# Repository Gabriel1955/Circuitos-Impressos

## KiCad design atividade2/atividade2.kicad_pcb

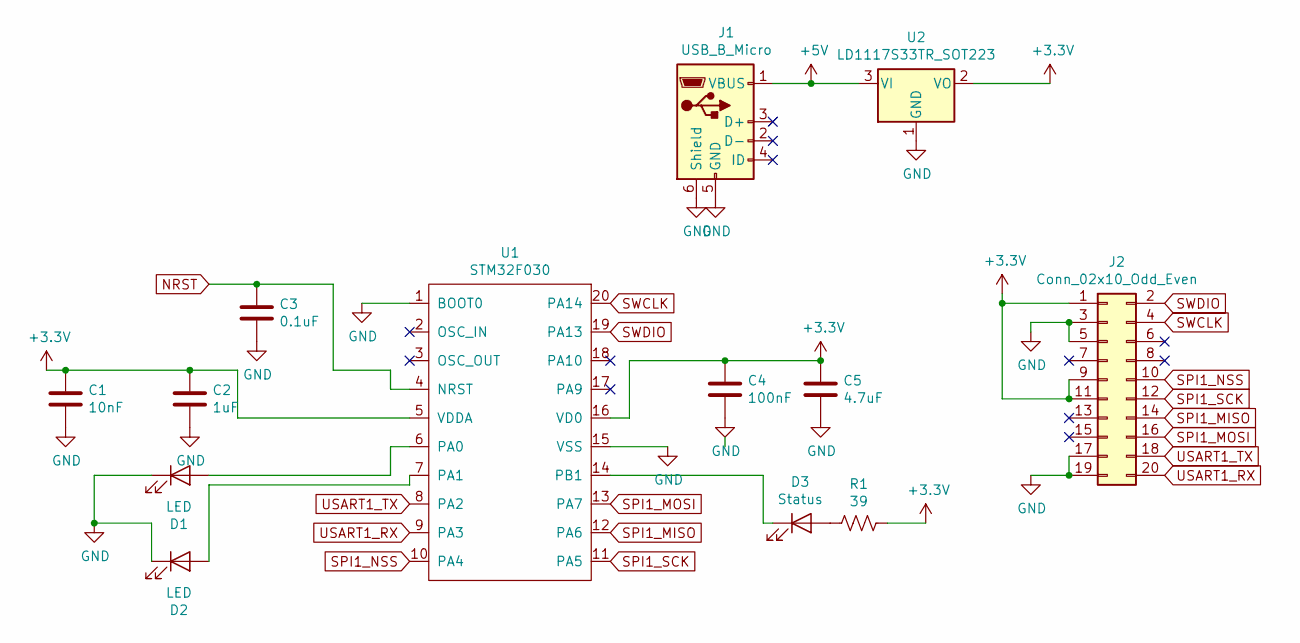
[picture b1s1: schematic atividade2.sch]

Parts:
C1: 10nF; C_0805_2012Metric_Pad1.15x1.40mm_HandSolder
C2: 1uF; C_0805_2012Metric_Pad1.15x1.40mm_HandSolder
C3: 0.1uF; C_0805_2012Metric_Pad1.15x1.40mm_HandSolder
C4: 100nF; C_0805_2012Metric_Pad1.15x1.40mm_HandSolder
C5: 4.7uF; C_0805_2012Metric_Pad1.15x1.40mm_HandSolder
D1, D2: LED; LED_0805_2012Metric_Pad1.15x1.40mm_HandSolder
D3: Status; LED_0805_2012Metric_Pad1.15x1.40mm_HandSolder
J1: USB_B_Micro; USB_Micro-B_Molex-105017-0001
J2: Conn_02x10_Odd_Even; PinHeader_2x10_P2.00mm_Vertical
R1: 39; R_0805_2012Metric_Pad1.15x1.40mm_HandSolder
U1: STM32F030; TSSOP-20_4.4x6.5mm_P0.65mm
U2: LD1117S33TR_SOT223; SOT-223-3_TabPin2

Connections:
+3V3: C1.1, C2.1, C4.1, C5.1, J2.1, J2.9, J2.11, R1.1, U1.5 (VDDA), U1.16 (VD0), U2.2 (VO)
+5V: J1.1 (VBUS), U2.3 (VI)
GND: C1.2, C2.2, C3.2, C4.2, C5.2, D1.1 (K), D2.1 (K), J1.5 (GND), J1.6 (Shield), J2.3, J2.5, J2.17, J2.19, U1.1 (BOOT0), U1.15 (VSS), U2.1 (GND)
NRST: C3.1, U1.4 (NRST)
unnamed: D1.2 (A), U1.6 (PA0)
unnamed: D2.2 (A), U1.7 (PA1)
unnamed: D3.1 (K), U1.14 (PB1)
unnamed: D3.2 (A), R1.2
SPI1_MISO: J2.14, U1.12 (PA6)
SPI1_MOSI: J2.16, U1.13 (PA7)
SPI1_NSS: J2.10, U1.10 (PA4)
SPI1_SCK: J2.12, U1.11 (PA5)
SWCLK: J2.4, U1.20 (PA14)
SWDIO: J2.2, U1.19 (PA13)
USART1_RX: J2.20, U1.9 (PA3)
USART1_TX: J2.18, U1.8 (PA2)

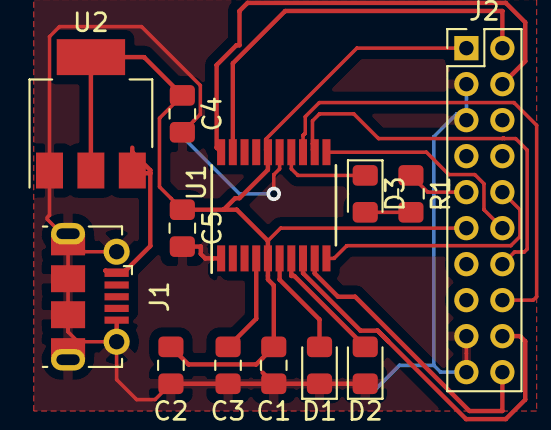
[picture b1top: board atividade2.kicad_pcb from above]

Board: 2 copper layers, 13 parts (0 on the bottom side), 16 nets.

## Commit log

2019-11-16 Send work
    Send work
2019-11-16 finished
